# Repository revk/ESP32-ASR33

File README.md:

# ESP32-ASR33

Now at [Codeberg](https://codeberg.org/RevK/ESP32-ASR33)

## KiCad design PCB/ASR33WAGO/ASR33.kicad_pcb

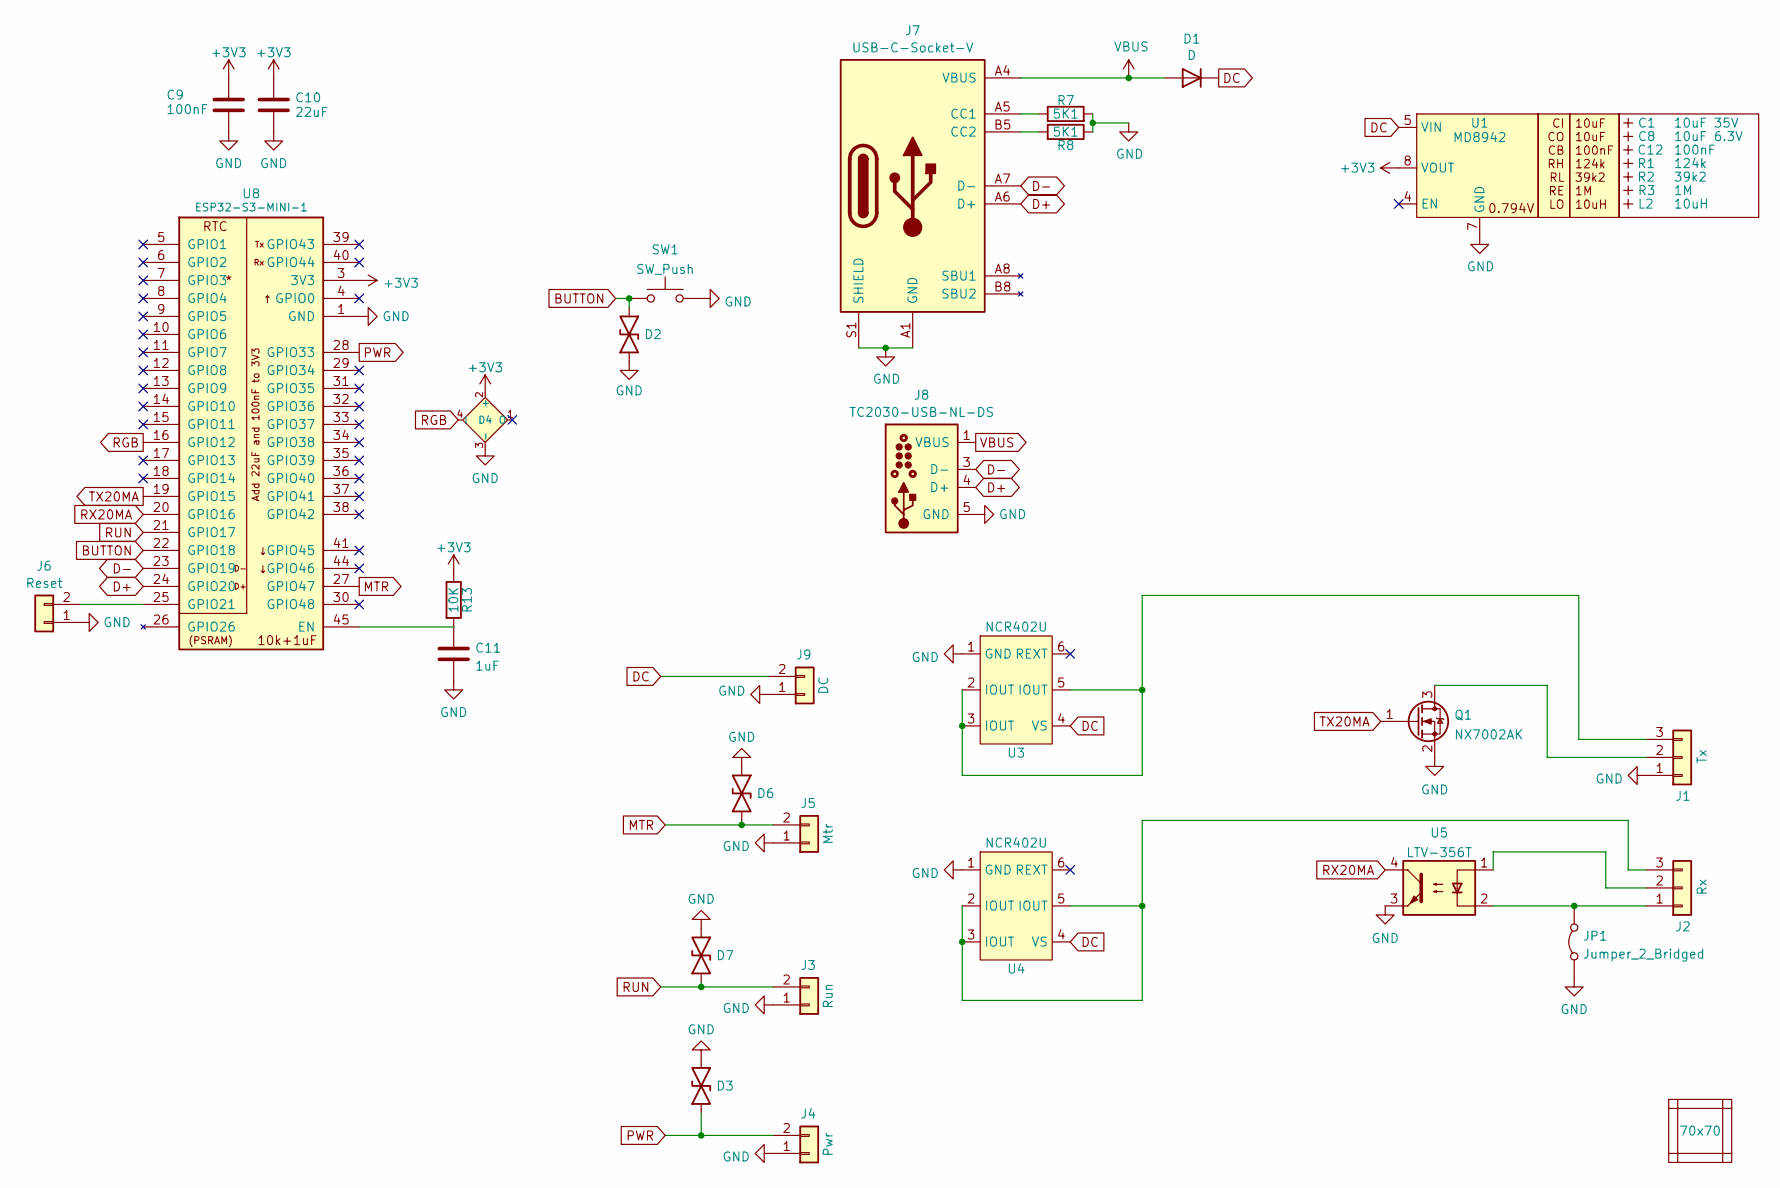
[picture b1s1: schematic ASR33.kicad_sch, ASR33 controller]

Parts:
C1: 10uF 35V; C_0603_; MPN C194427
C8: 10uF 6.3V; C_0603_; MPN C1691
C9: 100nF; C_0402
C10: 22uF; C_0402
C11: 1uF; C_0402
C12: 100nF; C_0603_
D1: D; D_SOD-123; MPN C1884542
D2, D3, D6, D7: DFN1006-2L; MPN C5137770
D4: XL-1010RGBC-WS2812B; SMD1010+; MPN C5349953
J1: Tx; WAGO-2060-453-998-404; MPN C2765056
J2: Rx; WAGO-2060-453-998-404; MPN C2765056
J3: Run; WAGO-2060-452-998-404; MPN C2765055
J4: Pwr; WAGO-2060-452-998-404; MPN C2765055
J5: Mtr; WAGO-2060-452-998-404; MPN C2765055
J6: Reset; AA-Pad
J7: USB-C-Socket-V; USB-C-Socket-H; MPN C709357
J8: TC2030-USB-NL-DS; Tag-Connect_TC2030-IDC-NL_2x03_P1.27mm_Vertical
J9: DC; WAGO-2060-452-998-404; MPN C2765055
JP1: Jumper_2_Bridged; Pad_1206_0805_Bridged
L2: 10uH; L_4x4_
PCB1: 70x70; PCB7070
Q1: NX7002AK; SOT-23
R1: 124k; R_0402_; MPN C138062
R2: 39k2; R_0402_
R3: 1M; R_0402_
R7, R8: 5K1; R_0402
R13: 10K; R_0402
SW1: SW_Push; TS-1092S-B3D2-G
U1: MD8942; SOT-23-6-MD8942; MPN C2684786
U3, U4: NCR402U; SOT-457; MPN C458148
U5: LTV-356T; SO-4_4.4x3.6mm_P2.54mm
U8: ESP32-S3-MINI-1; MPN C3013941
V1, V2, V3, V4: VCUT70N

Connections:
+3V3: C9.1, C10.1, D4.2 (+), R13.1, U1.8 (VOUT), U8.3 (3V3)
BUTTON: D2.1, SW1.2, U8.22 (GPIO18)
D+: J7.A6 (D+), J7.B6 (D+), J8.4 (D+), U8.24 (GPIO20)
D-: J7.A7 (D-), J7.B7 (D-), J8.3 (D-), U8.23 (GPIO19)
DC: D1.1 (K), J9.2, U1.5 (VIN), U3.4 (VS), U4.4 (VS)
GND: C9.2, C10.2, C11.2, D2.2, D3.2, D4.3 (-), D6.2, D7.2, J1.1, J3.1, J4.1, J5.1, J6.1, J7.A1 (GND), J7.A12 (GND), J7.B1 (GND), J7.B12 (GND), J7.S1 (SHIELD), J8.5 (GND), J8.6 (GND), J9.1, JP1.1 (A), Q1.2 (S), R7.2, R8.1, SW1.1, U1.2 (GND), U1.7 (GND), U3.1 (GND), U4.1 (GND), U5.3, U8.1 (GND), U8.2 (GND), U8.42 (GND), U8.43 (GND), U8.46 (GND), U8.47 (GND), U8.48 (GND), U8.49 (GND), U8.50 (GND), U8.51 (GND), U8.52 (GND), U8.53 (GND), U8.54 (GND), U8.55 (GND), U8.56 (GND), U8.57 (GND), U8.58 (GND), U8.59 (GND), U8.60 (GND), U8.61 (GND), U8.62 (GND), U8.63 (GND), U8.64 (GND), U8.65 (GND)
MTR: D6.1, J5.2, U8.27 (GPIO47)
unnamed: J1.2, Q1.3 (D)
unnamed: J1.3, U3.2 (IOUT), U3.3 (IOUT), U3.5 (IOUT)
unnamed: J2.1, JP1.2 (B), U5.2
unnamed: J2.2, U5.1
unnamed: J2.3, U4.2 (IOUT), U4.3 (IOUT), U4.5 (IOUT)
unnamed: J6.2, U8.25 (GPIO21)
unnamed: J7.A5 (CC1), R7.1
unnamed: J7.B5 (CC2), R8.2
unnamed: C11.1, R13.2, U8.45 (EN)
PWR: D3.1, J4.2, U8.28 (GPIO33)
RGB: D4.4 (I), U8.16 (GPIO12)
RUN: D7.1, J3.2, U8.21 (GPIO17)
RX20MA: U5.4, U8.20 (GPIO16)
TX20MA: Q1.1 (G), U8.19 (GPIO15)
VBUS: D1.2 (A), J7.A4 (VBUS), J7.A9 (VBUS), J7.B4 (VBUS), J7.B9 (VBUS), J8.1 (VBUS), J8.2 (VBUS)

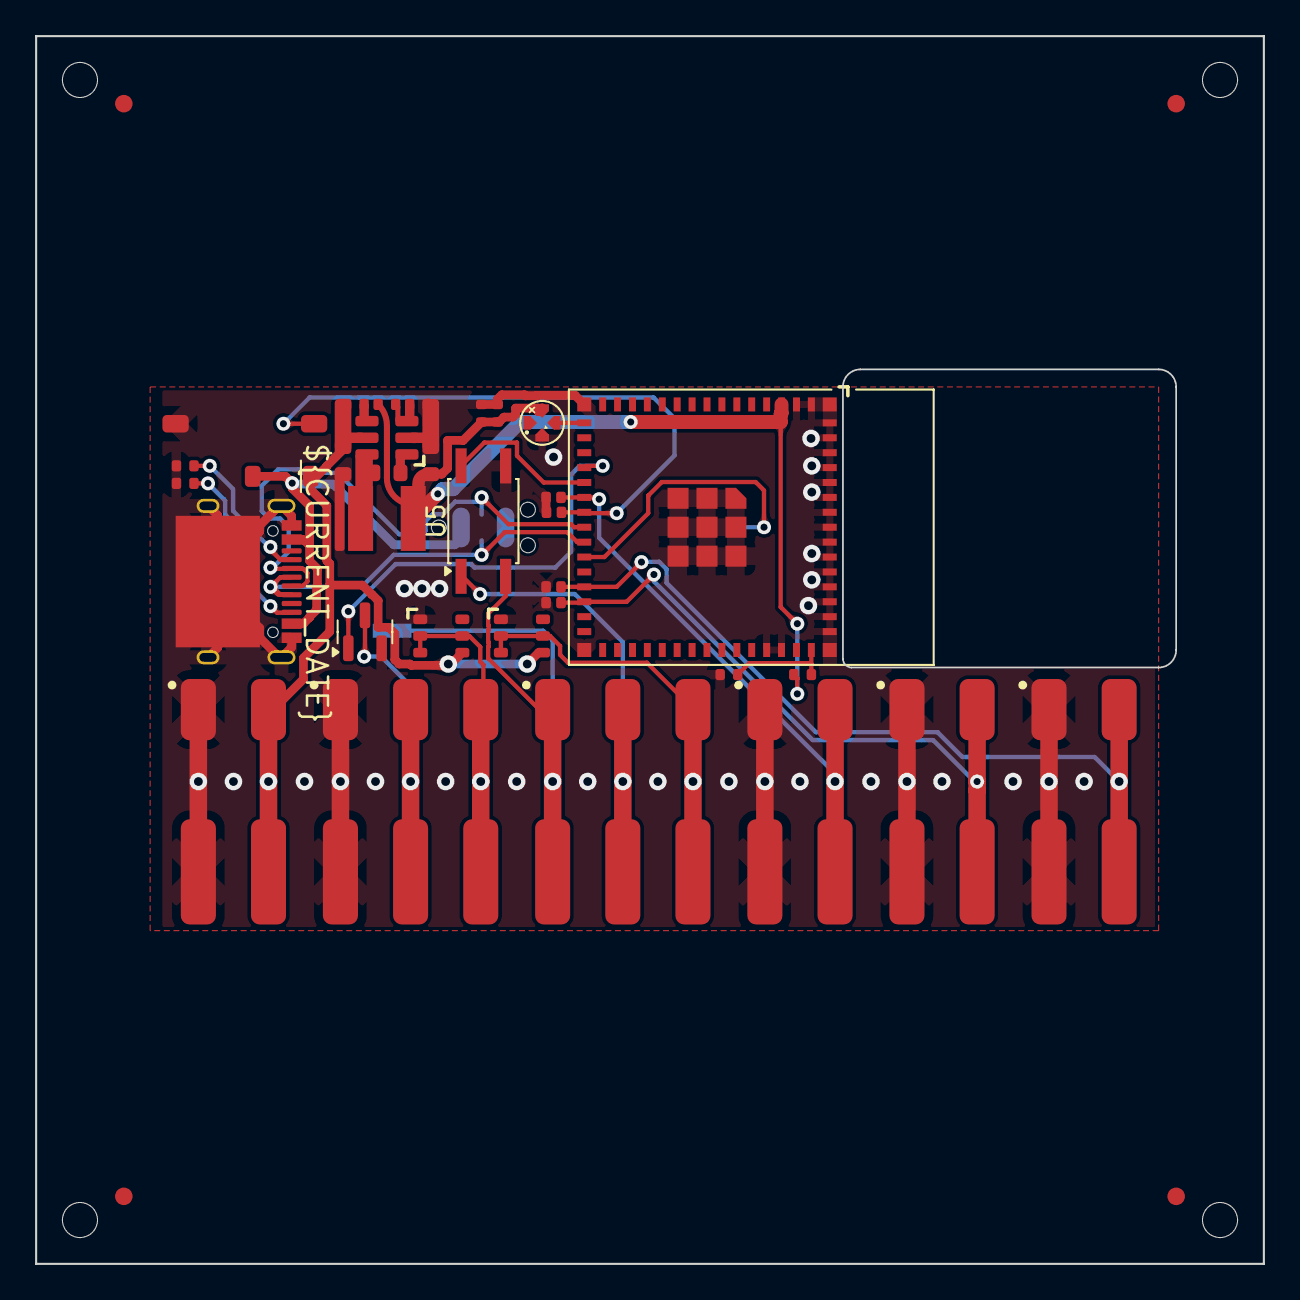
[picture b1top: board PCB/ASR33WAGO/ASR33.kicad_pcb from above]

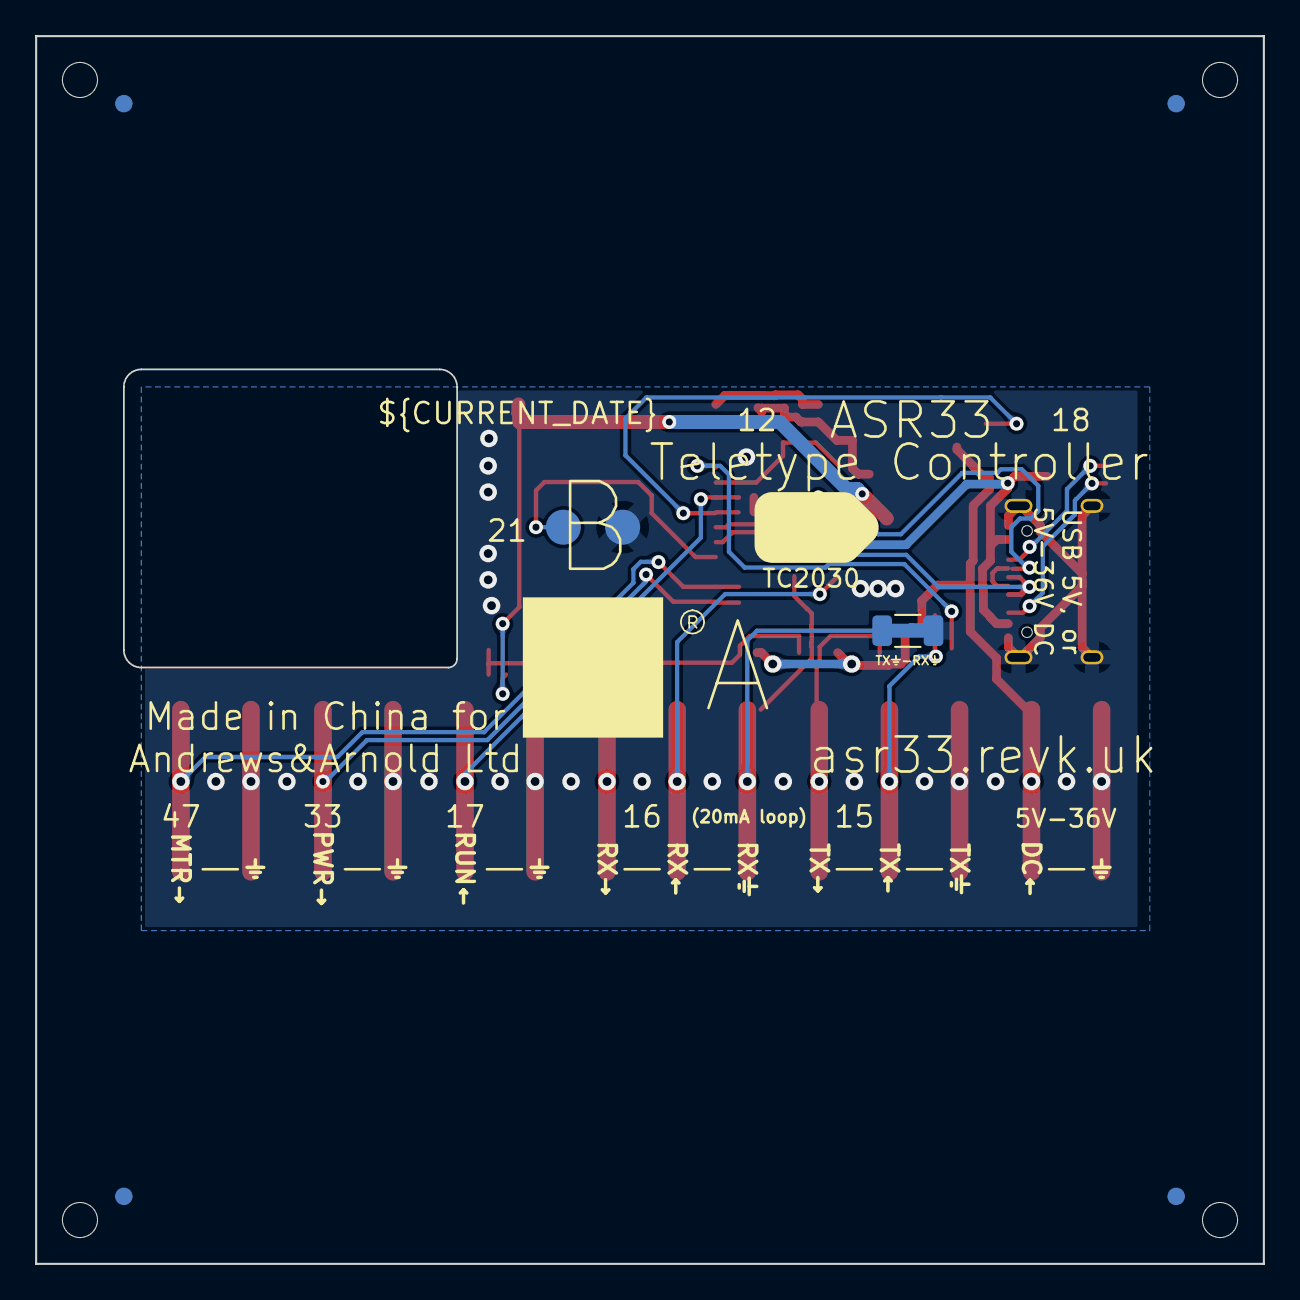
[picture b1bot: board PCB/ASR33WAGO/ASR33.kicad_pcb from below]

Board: 2 copper layers, 70.0 x 70.0 mm, 41 parts (3 on the bottom side), 22 nets.

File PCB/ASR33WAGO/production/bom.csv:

Designator,Footprint,Quantity,Value,LCSC Part #
C1,C_0603_,1,10uF 35V,C194427
C10,C_0402,1,22uF,
C11,C_0402,1,1uF,
C12,C_0603_,1,100nF,
C8,C_0603_,1,10uF 6.3V,C1691
C9,C_0402,1,100nF,
D1,D_SOD-123,1,D,C1884542
"D2, D3, D6, D7",DFN1006-2L,4,~,C5137770
D4,SMD1010+,1,XL-1010RGBC-WS2812B,C5349953
J1,WAGO-2060-453-998-404,1,Tx,C2765056
J2,WAGO-2060-453-998-404,1,Rx,C2765056
J3,WAGO-2060-452-998-404,1,Run,C2765055
J4,WAGO-2060-452-998-404,1,Pwr,C2765055
J5,WAGO-2060-452-998-404,1,Mtr,C2765055
J7,USB-C-Socket-H,1,USB-C-Socket-V,C709357
J9,WAGO-2060-452-998-404,1,DC,C2765055
L2,L_4x4_,1,10uH,
Q1,SOT-23,1,NX7002AK,
R1,R_0402_,1,124k,C138062
R13,R_0402,1,10K,
R2,R_0402_,1,39k2,
R3,R_0402_,1,1M,
"R7, R8",R_0402,2,5K1,
SW1,TS-1092S-B3D2-G,1,SW_Push,
U1,SOT-23-6-MD8942,1,MD8942,C2684786
"U3, U4",SOT-457,2,NCR402U,C458148
U5,SO-4_4.4x3.6mm_P2.54mm,1,LTV-356T,
U8,ESP32-S3-MINI-1,1,ESP32-S3-MINI-1,C3013941

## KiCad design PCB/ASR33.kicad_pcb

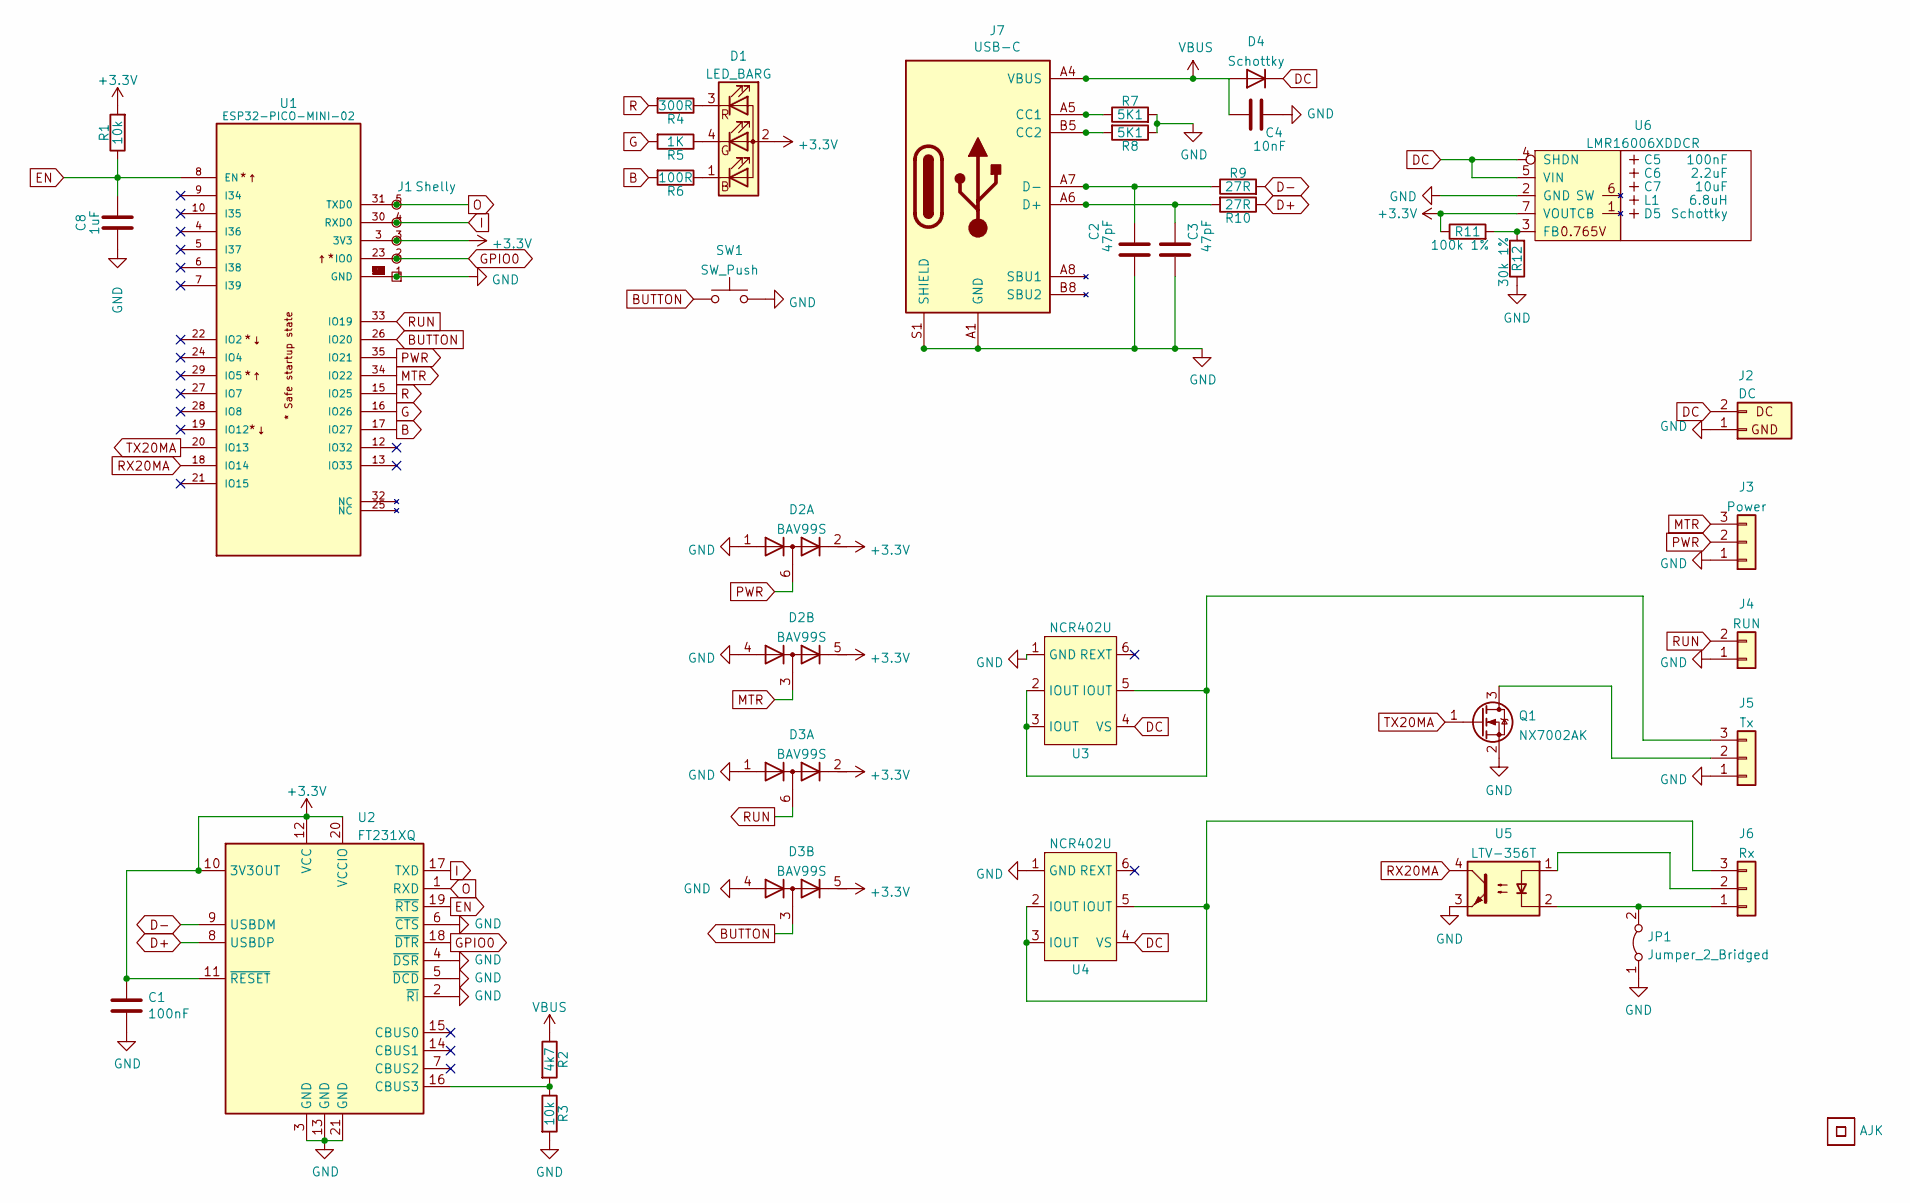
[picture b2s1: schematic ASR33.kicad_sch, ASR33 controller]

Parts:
C1: 100nF; C_0603
C2, C3: 47pF; C_0603
C4: 10nF; C_0603
C5: 100nF; C_0603_; LCSC Part # C30926
C6: 2.2uF; C_0805_; LCSC Part # C19110
C7: 10uF; C_0805_; LCSC Part # C17024
C8: 1uF; C_0603
D1: LED_BARG; MHS190RGBCT; LCSC Part # C409798
D2, D3: BAV99S; SOT-363_SC-70-6; JLCPCB Rotation Offset -90
D4: Schottky; D_1206; LCSC Part # C143805
D5: Schottky; D_1206_; LCSC Part # C143805
J1: Shelly
J2: DC; PTSM-HH1-2-RA
J3: Power; PTSM-HH1-3-RA
J4: RUN; PTSM-HH1-2-RA
J5: Tx; PTSM-HH1-3-RA
J6: Rx; PTSM-HH1-3-RA
J7: USB-C; USC16-TR; LCSC Part # C709357
JP1: Jumper_2_Bridged; Pad_1206_0805_Bridged
L1: 6.8uH; L_4x4_; LCSC Part # C354575
Logo1: AJK
Q1: NX7002AK; SOT-23; JLCPCB Rotation Offset 180
R1, R3: 10k; R_0603
R2: 4k7; R_0603
R4: 300R; R_0603; Part No 0603-680R
R5: 1K; R_0603; Part No 0603-2K
R6: 100R; R_0603; Part No 0603-220R
R7, R8: 5K1; R_0603
R9, R10: 27R; R_0603
R11: 100k 1%; R_0603; LCSC Part # C14675
R12: 30k 1%; R_0603; LCSC Part # C100001
SW1: SW_Push; SW_PUSH_6mm_PTH
U1: ESP32-PICO-MINI-02; PARTREV v1.0; LCSC Part # C2980306
U2: FT231XQ; QFN-20-1EP_4x4mm_P0.5mm_EP2.5x2.5mm; LCSC Part # C132159
U3, U4: NCR402U; SOT-457; JLCPCB Rotation Offset -90
U5: LTV-356T; SO-4_4.4x3.6mm_P2.54mm; JLCPCB Rotation Offset -90
U6: LMR16006XDDCR; SOT-23-Thin-6-Reg; Part No LMR16006XDDCR; LCSC Part # C87080
U7: QR; QR-ASR33

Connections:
+3V3: C1.1, D1.2 (A), D2.2 (K2), D2.5 (K4), D3.2 (K2), D3.5 (K4), J1.3 (3V3), R1.2, R11.1, U1.3 (3V3), U2.10 (3V3OUT), U2.11 (~RESET), U2.12 (VCC), U2.20 (VCCIO), U6.7 (VOUT)
B: R6.2, U1.17 (IO27)
BUTTON: D3.3 (K1A2), SW1.2, U1.26 (IO20)
D+: R10.1, U2.8 (USBDP)
D-: R9.2, U2.9 (USBDM)
DC: D4.1 (K), J2.2 (DC), U3.4 (VS), U4.4 (VS), U6.4 (SHDN), U6.5 (VIN)
EN: C8.2, R1.1, U1.8 (EN), U2.19 (~RTS)
G: R5.2, U1.16 (IO26)
GND: C1.2, C2.2, C3.2, C4.1, C8.1, D2.1 (A1), D2.4 (A3), D3.1 (A1), D3.4 (A3), J1.1 (GND), J2.1 (GND), J3.1, J4.1, J5.1, J7.A1 (GND), J7.A12 (GND), J7.B1 (GND), J7.B12 (GND), J7.S1 (SHIELD), JP1.1 (A), Q1.2 (S), R3.2, R7.2, R8.1, R12.1, SW1.1, U1.1 (GND), U1.2 (GND), U1.11 (GND), U1.14 (GND), U1.36 (GND), U1.37 (GND), U1.38 (GND), U1.39 (GND), U1.40 (GND), U1.41 (GND), U1.42 (GND), U1.43 (GND), U1.44 (GND), U1.45 (GND), U1.46 (GND), U1.47 (GND), U1.48 (GND), U1.49 (GND), U1.50 (GND), U1.51 (GND), U1.52 (GND), U1.53 (GND), U2.2 (~RI), U2.3 (GND), U2.4 (~DSR), U2.5 (~DCD), U2.6 (~CTS), U2.13 (GND), U2.21 (GND), U3.1 (GND), U4.1 (GND), U5.3, U6.2 (GND)
GPIO0: J1.2 (0), U1.23 (IO0), U2.18 (~DTR)
I: J1.4 (Rx), U1.30 (RXD0), U2.17 (TXD)
MTR: D2.3 (K1A2), J3.3, U1.34 (IO22)
unnamed: C2.1, J7.A7 (D-), J7.B7 (D-), R9.1
unnamed: C3.1, J7.A6 (D+), J7.B6 (D+), R10.2
unnamed: D1.1 (BK), R6.1
unnamed: D1.4 (GK), R5.1
unnamed: D1.3 (RK), R4.1
unnamed: J5.2, Q1.3 (D)
unnamed: J5.3, U3.2 (IOUT), U3.3 (IOUT), U3.5 (IOUT)
unnamed: J6.1, JP1.2 (B), U5.2
unnamed: J6.2, U5.1
unnamed: J6.3, U4.2 (IOUT), U4.3 (IOUT), U4.5 (IOUT)
unnamed: J7.A5 (CC1), R7.1
unnamed: J7.B5 (CC2), R8.2
unnamed: R2.2, R3.1, U2.16 (CBUS3)
unnamed: R11.2, R12.2, U6.3 (FB)
O: J1.5 (Tx), U1.31 (TXD0), U2.1 (RXD)
PWR: D2.6 (K3A4), J3.2, U1.35 (IO21)
R: R4.2, U1.15 (IO25)
RUN: D3.6 (K3A4), J4.2, U1.33 (IO19)
RX20MA: U1.18 (IO14), U5.4
TX20MA: Q1.1 (G), U1.20 (IO13)
VBUS: C4.2, D4.2 (A), J7.A4 (VBUS), J7.A9 (VBUS), J7.B4 (VBUS), J7.B9 (VBUS), R2.1

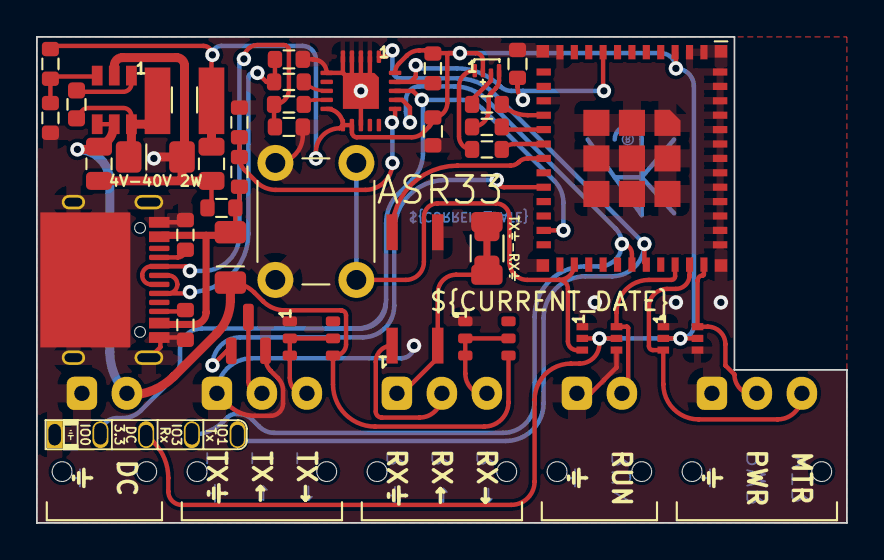
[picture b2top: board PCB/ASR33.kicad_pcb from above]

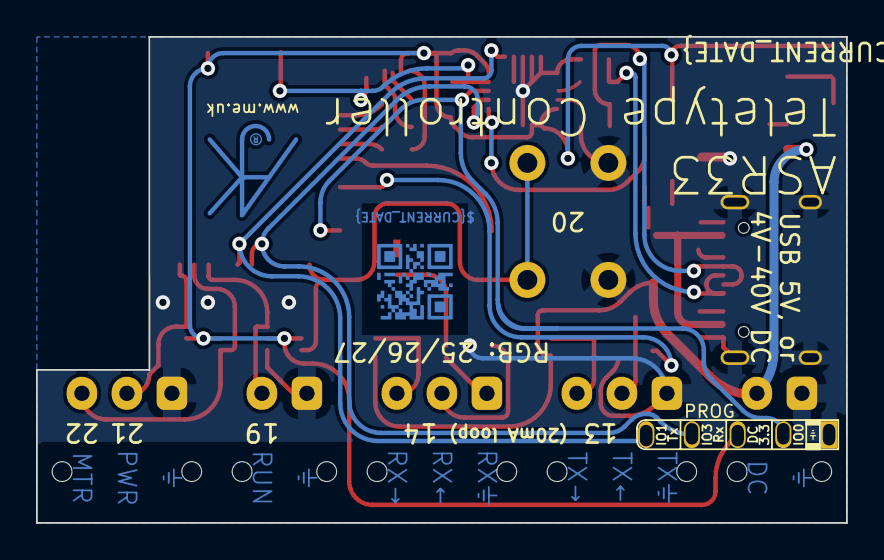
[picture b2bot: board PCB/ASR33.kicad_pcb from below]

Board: 2 copper layers, 45.0 x 27.0 mm, 44 parts (2 on the bottom side), 33 nets.

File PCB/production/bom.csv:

Designator,Footprint,Quantity,Value,LCSC Part #
C1,C_0603,1,100nF,
"C2, C3",C_0603,2,47pF,
C4,C_0603,1,10nF,
C5,C_0603_,1,100nF,C30926
C6,C_0805_,1,2.2uF,C19110
C7,C_0805_,1,10uF,C17024
D1,MHS190RGBCT,1,LED_BARG,C409798
"D2, D3",SOT-363_SC-70-6,2,BAV99S,
D4,D_1206,1,Schottky,C143805
D5,D_1206_,1,Schottky,C143805
J2,PTSM-HH1-2-RA,1,DC,
J3,PTSM-HH1-3-RA,1,Power,
J4,PTSM-HH1-2-RA,1,RUN,
J5,PTSM-HH1-3-RA,1,Tx,
J6,PTSM-HH1-3-RA,1,Rx,
J7,USC16-TR,1,USB-C,C709357
L1,L_4x4_,1,6.8uH,C354575
Q1,SOT-23,1,NX7002AK,
"R1, R3",R_0603,2,10k,
"R10, R9",R_0603,2,27R,
R11,R_0603,1,100k 1%,C14675
R12,R_0603,1,30k 1%,C100001
R2,R_0603,1,4k7,
R4,R_0603,1,300R,
R5,R_0603,1,1K,
R6,R_0603,1,100R,
"R7, R8",R_0603,2,5K1,
SW1,SW_PUSH_6mm_PTH,1,SW_Push,
U1,ESP32-PICO-MINI-02,1,ESP32-PICO-MINI-02,C2980306
U2,QFN-20-1EP_4x4mm_P0.5mm_EP2.5x2.5mm,1,FT231XQ,C132159
"U3, U4",SOT-457,2,NCR402U,
U5,SO-4_4.4x3.6mm_P2.54mm,1,LTV-356T,
U6,SOT-23-Thin-6-Reg,1,LMR16006XDDCR,C87080

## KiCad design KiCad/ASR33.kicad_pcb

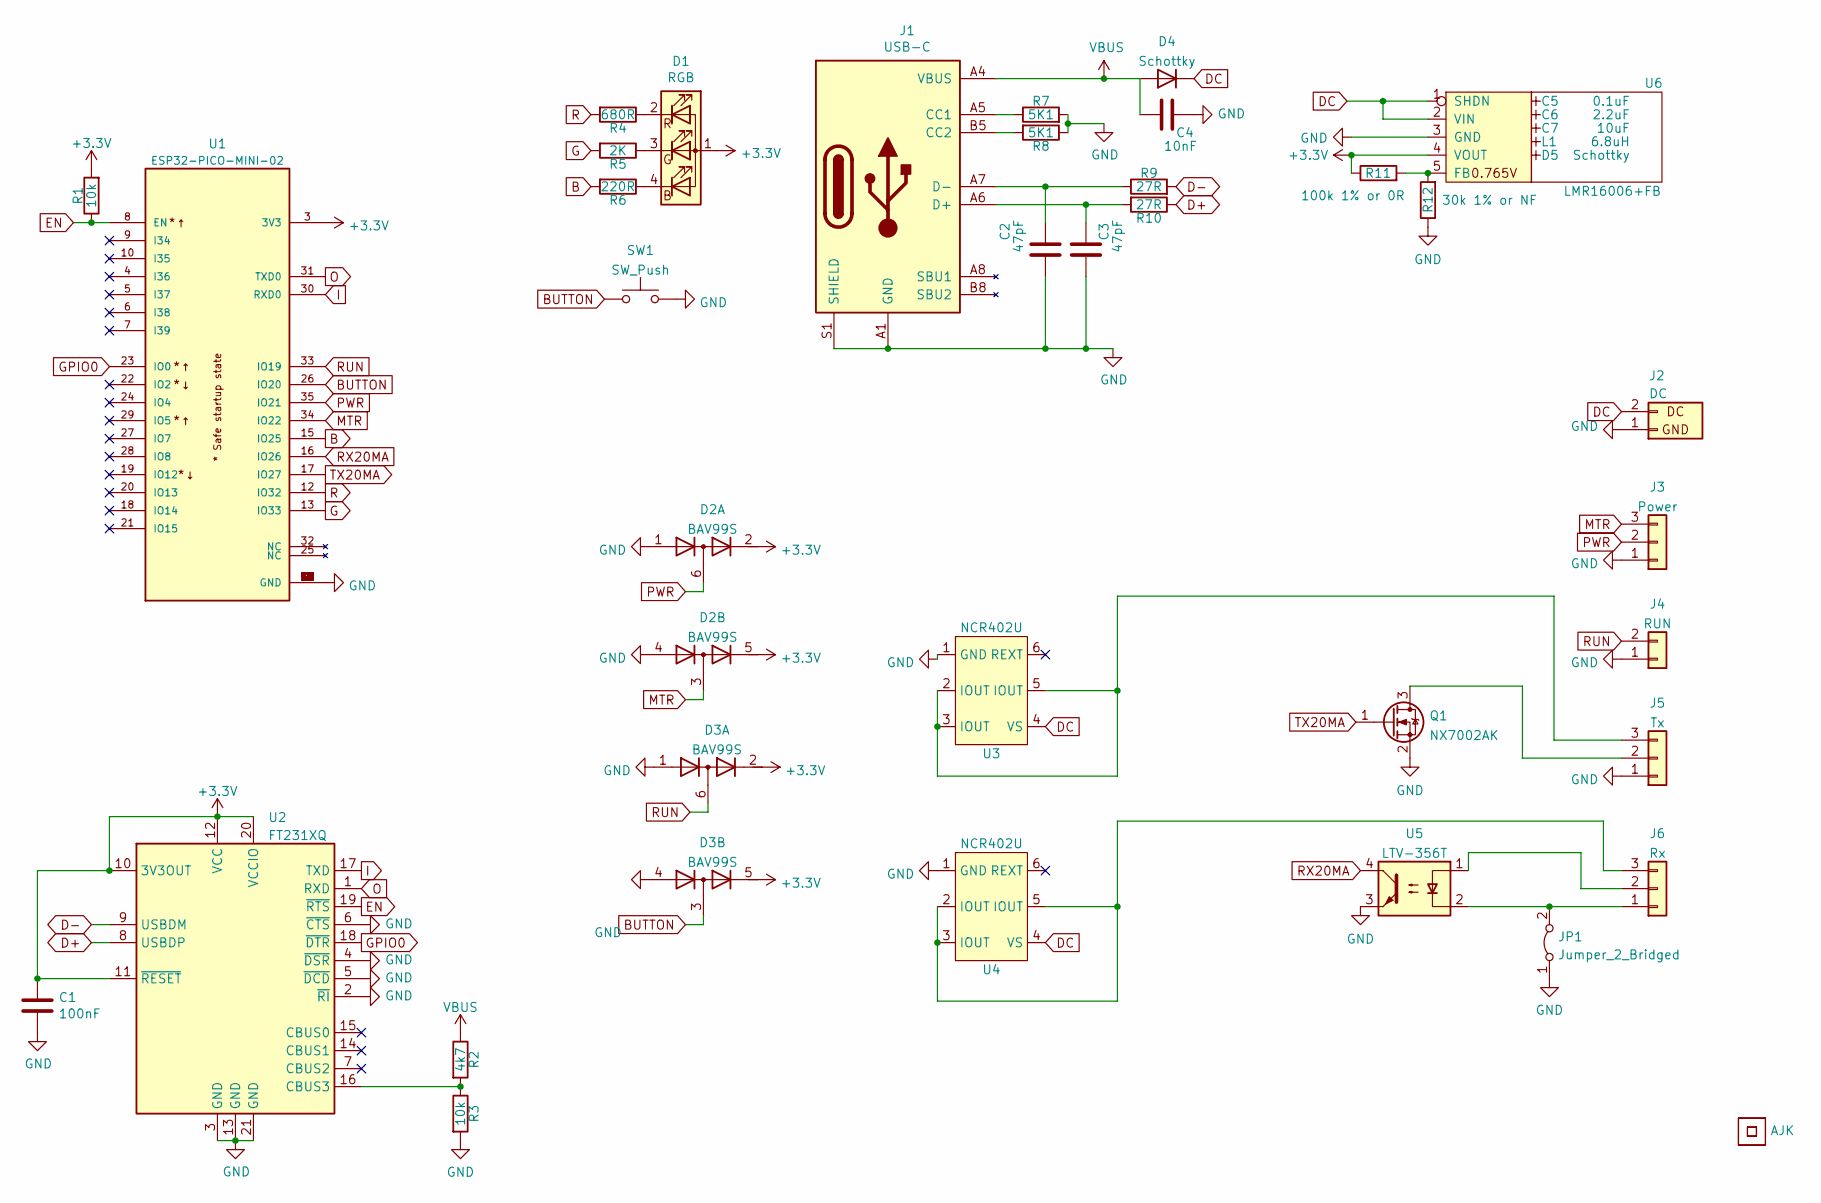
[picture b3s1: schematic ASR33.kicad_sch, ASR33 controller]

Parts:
C1: 100nF; C_0603
C2, C3: 47pF; C_0603
C4: 10nF; C_0603
C5: 0.1uF; Hidden
C6: 2.2uF; Hidden
C7: 10uF; Hidden
D1: RGB; LED-RGB-1.6x1.6; Part No APTF1616LSEEZGKQBKC
D2, D3: BAV99S; SOT-363_SC-70-6
D4: Schottky; D_1206
D5: Schottky; Hidden; Part No CD1206-B2100
J1: USB-C; USC16-TR-Round; Part No CSP-USC16-TR
J2: DC; Molex_MiniSPOX_H2RA
J3: Power; Molex_MiniSPOX_H3RA
J4: RUN; Molex_MiniSPOX_H2RA
J5: Tx; Molex_MiniSPOX_H3RA
J6: Rx; Molex_MiniSPOX_H3RA
JP1: Jumper_2_Bridged; Pad_1206_0805_Bridged
L1: 6.8uH; Hidden; Part No TYA4020
Logo1: AJK
Q1: NX7002AK; SOT-23
R1, R3: 10k; R_0603
R2: 4k7; R_0603
R4: 680R; R_0603
R5: 2K; R_0603
R6: 220R; R_0603
R7, R8: 5K1; R_0603
R9, R10: 27R; R_0603
R11: 100k 1% or 0R; R_0603
R12: 30k 1% or NF; R_0603
SW1: SW_Push; SW_PUSH_6mm_PTH
U1: ESP32-PICO-MINI-02; PARTREV v1.0
U2: FT231XQ; QFN-20-1EP_4x4mm_P0.5mm_EP2.5x2.5mm
U3, U4: NCR402U; SOT-457
U5: LTV-356T; SO-4_4.4x3.6mm_P2.54mm
U6: LMR16006+FB; RegulatorBlockFB; Part No LMR16006YQ3
U7: QR; QR-ASR33

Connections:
+3V3: C1.1, D1.1 (A), D2.2 (K2), D2.5 (K4), D3.2 (K2), D3.5 (K4), R1.2, R11.1, U1.3 (3V3), U2.10 (3V3OUT), U2.11 (~RESET), U2.12 (VCC), U2.20 (VCCIO), U6.4 (VOUT)
B: R6.2, U1.15 (IO25)
BUTTON: D3.3 (K1A2), SW1.2, U1.26 (IO20)
D+: R10.1, U2.8 (USBDP)
D-: R9.2, U2.9 (USBDM)
DC: D4.1 (K), J2.2 (DC), U3.4 (VS), U4.4 (VS), U6.1 (SHDN), U6.2 (VIN)
EN: R1.1, U1.8 (EN), U2.19 (~RTS)
G: R5.2, U1.13 (IO33)
GND: C1.2, C2.2, C3.2, C4.1, D2.1 (A1), D2.4 (A3), D3.1 (A1), D3.4 (A3), J1.A1 (GND), J1.A12 (GND), J1.B1 (GND), J1.B12 (GND), J1.S1 (SHIELD), J2.1 (GND), J3.1, J4.1, J5.1, JP1.1 (A), Q1.2 (S), R3.2, R7.2, R8.1, R12.1, SW1.1, U1.1 (GND), U1.2 (GND), U1.11 (GND), U1.14 (GND), U1.36 (GND), U1.37 (GND), U1.38 (GND), U1.39 (GND), U1.40 (GND), U1.41 (GND), U1.42 (GND), U1.43 (GND), U1.44 (GND), U1.45 (GND), U1.46 (GND), U1.47 (GND), U1.48 (GND), U1.49 (GND), U1.50 (GND), U1.51 (GND), U1.52 (GND), U1.53 (GND), U2.2 (~RI), U2.3 (GND), U2.4 (~DSR), U2.5 (~DCD), U2.6 (~CTS), U2.13 (GND), U2.21 (GND), U3.1 (GND), U4.1 (GND), U5.3, U6.3 (GND)
GPIO0: U1.23 (IO0), U2.18 (~DTR)
I: U1.30 (RXD0), U2.17 (TXD)
MTR: D2.3 (K1A2), J3.3, U1.34 (IO22)
unnamed: C2.1, J1.A7 (D-), J1.B7 (D-), R9.1
unnamed: C3.1, J1.A6 (D+), J1.B6 (D+), R10.2
unnamed: D1.2 (RK), R4.1
unnamed: D1.3 (GK), R5.1
unnamed: D1.4 (BK), R6.1
unnamed: J1.A5 (CC1), R7.1
unnamed: J1.B5 (CC2), R8.2
unnamed: J5.2, Q1.3 (D)
unnamed: J5.3, U3.2 (IOUT), U3.3 (IOUT), U3.5 (IOUT)
unnamed: J6.1, JP1.2 (B), U5.2
unnamed: J6.2, U5.1
unnamed: J6.3, U4.2 (IOUT), U4.3 (IOUT), U4.5 (IOUT)
unnamed: R2.2, R3.1, U2.16 (CBUS3)
unnamed: R11.2, R12.2, U6.5 (FB)
O: U1.31 (TXD0), U2.1 (RXD)
PWR: D2.6 (K3A4), J3.2, U1.35 (IO21)
R: R4.2, U1.12 (IO32)
RUN: D3.6 (K3A4), J4.2, U1.33 (IO19)
RX20MA: U1.16 (IO26), U5.4
TX20MA: Q1.1 (G), U1.17 (IO27)
VBUS: C4.2, D4.2 (A), J1.A4 (VBUS), J1.A9 (VBUS), J1.B4 (VBUS), J1.B9 (VBUS), R2.1

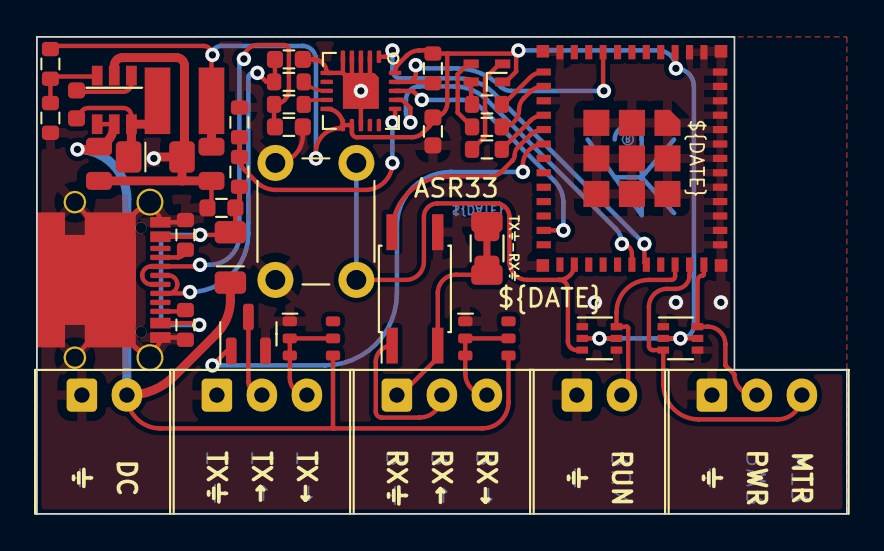
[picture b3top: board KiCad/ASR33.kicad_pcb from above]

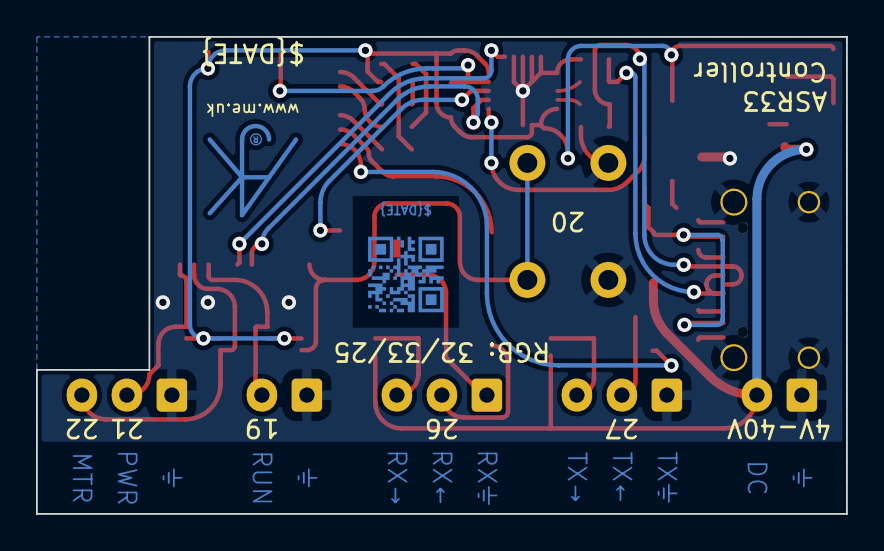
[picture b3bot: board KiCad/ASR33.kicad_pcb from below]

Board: 2 copper layers, 45.0 x 26.5 mm, 42 parts (2 on the bottom side), 33 nets.

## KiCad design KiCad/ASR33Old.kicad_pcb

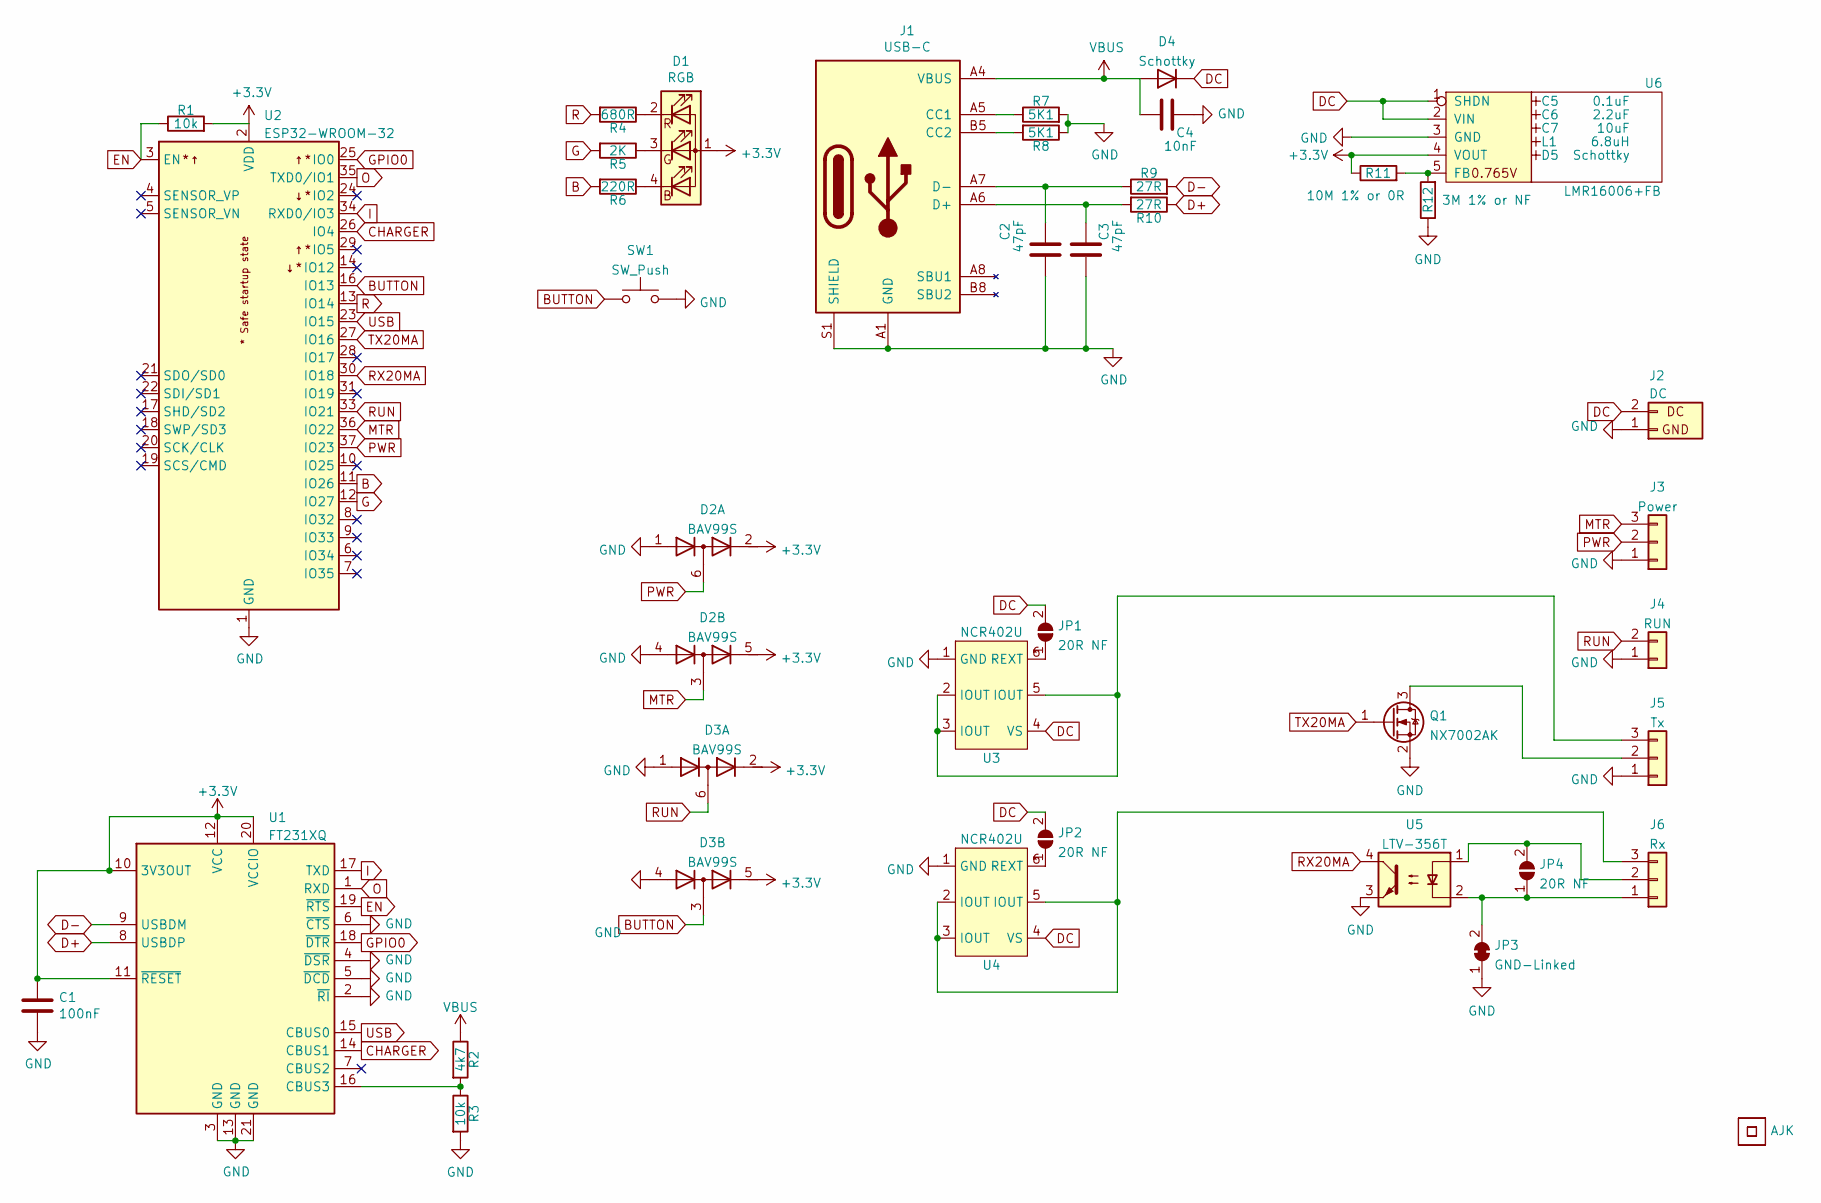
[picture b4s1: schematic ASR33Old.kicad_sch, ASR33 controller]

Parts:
C1: 100nF; C_0603
C2, C3: 47pF; C_0603
C4: 10nF; C_0603
C5: 0.1uF; Hidden
C6: 2.2uF; Hidden
C7: 10uF; Hidden
D1: RGB; LED-RGB-1.6x1.6; Part No APTF1616LSEEZGKQBKC
D2, D3: BAV99S; SOT-363_SC-70-6
D4: Schottky; D_1206_3216Metric
D5: Schottky; Hidden; Part No CD1206-B2100
J1: USB-C; USC16-TR-Round; Part No CSP-USC16-TR
J2: DC; Molex_MiniSPOX_H2RA
J3: Power; Molex_MiniSPOX_H3RA
J4: RUN; Molex_MiniSPOX_H2RA
J5: Tx; Molex_MiniSPOX_H3RA
J6: Rx; Molex_MiniSPOX_H3RA
JP1, JP2, JP4: 20R NF; Pad_1206_0805_Open
JP3: GND-Linked; Pad_1206_0805_Bridged
L1: 6.8uH; Hidden; Part No TYA4020
Logo1: AJK
Q1: NX7002AK; SOT-23
R1, R3: 10k; R_0603
R2: 4k7; R_0603
R4: 680R; R_0603
R5: 2K; R_0603
R6: 220R; R_0603
R7, R8: 5K1; R_0603
R9, R10: 27R; R_0603
R11: 10M 1% or 0R; R_0603
R12: 3M 1% or NF; R_0603
SW1: SW_Push; SW_PUSH_6mm_PTH
U1: FT231XQ; QFN-20-1EP_4x4mm_P0.5mm_EP2.5x2.5mm
U2: ESP32-WROOM-32
U3, U4: NCR402U; SOT-457
U5: LTV-356T; SO-4_4.4x3.6mm_P2.54mm
U6: LMR16006+FB; RegulatorBlockFB; Part No LMR16006YQ3
U7: QR; QR-ASR33

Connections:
+3V3: C1.1, D1.1 (A), D2.2 (K2), D2.5 (K4), D3.2 (K2), D3.5 (K4), R1.2, R11.1, U1.10 (3V3OUT), U1.11 (~RESET), U1.12 (VCC), U1.20 (VCCIO), U2.2 (VDD), U6.4 (VOUT)
B: R6.2, U2.11 (IO26)
BUTTON: D3.3 (K1A2), SW1.2, U2.16 (IO13)
CHARGER: U1.14 (CBUS1), U2.26 (IO4)
D+: R10.1, U1.8 (USBDP)
D-: R9.2, U1.9 (USBDM)
DC: D4.1 (K), J2.2 (DC), JP1.2 (B), JP2.2 (B), U3.4 (VS), U4.4 (VS), U6.1 (SHDN), U6.2 (VIN)
EN: R1.1, U1.19 (~RTS), U2.3 (EN)
G: R5.2, U2.12 (IO27)
GND: C1.2, C2.2, C3.2, C4.1, D2.1 (A1), D2.4 (A3), D3.1 (A1), D3.4 (A3), J1.A1 (GND), J1.A12 (GND), J1.B1 (GND), J1.B12 (GND), J1.S1 (SHIELD), J2.1 (GND), J3.1, J4.1, J5.1, JP3.1 (A), Q1.2 (S), R3.2, R7.2, R8.1, R12.1, SW1.1, U1.2 (~RI), U1.3 (GND), U1.4 (~DSR), U1.5 (~DCD), U1.6 (~CTS), U1.13 (GND), U1.21 (GND), U2.1 (GND), U2.15 (GND), U2.38 (GND), U2.39 (GND), U3.1 (GND), U4.1 (GND), U5.3, U6.3 (GND)
GPIO0: U1.18 (~DTR), U2.25 (IO0)
I: U1.17 (TXD), U2.34 (RXD0/IO3)
MTR: D2.3 (K1A2), J3.3, U2.36 (IO22)
unnamed: C2.1, J1.A7 (D-), J1.B7 (D-), R9.1
unnamed: C3.1, J1.A6 (D+), J1.B6 (D+), R10.2
unnamed: D1.2 (RK), R4.1
unnamed: D1.3 (GK), R5.1
unnamed: D1.4 (BK), R6.1
unnamed: J1.A5 (CC1), R7.1
unnamed: J1.B5 (CC2), R8.2
unnamed: J5.2, Q1.3 (D)
unnamed: J5.3, U3.2 (IOUT), U3.3 (IOUT), U3.5 (IOUT)
unnamed: J6.1, JP3.2 (B), JP4.1 (A), U5.2
unnamed: J6.2, JP4.2 (B), U5.1
unnamed: J6.3, U4.2 (IOUT), U4.3 (IOUT), U4.5 (IOUT)
unnamed: JP1.1 (A), U3.6 (REXT)
unnamed: JP2.1 (A), U4.6 (REXT)
unnamed: R2.2, R3.1, U1.16 (CBUS3)
unnamed: R11.2, R12.2, U6.5 (FB)
O: U1.1 (RXD), U2.35 (TXD0/IO1)
PWR: D2.6 (K3A4), J3.2, U2.37 (IO23)
R: R4.2, U2.13 (IO14)
RUN: D3.6 (K3A4), J4.2, U2.33 (IO21)
RX20MA: U2.30 (IO18), U5.4
TX20MA: Q1.1 (G), U2.27 (IO16)
USB: U1.15 (CBUS0), U2.23 (IO15)
VBUS: C4.2, D4.2 (A), J1.A4 (VBUS), J1.A9 (VBUS), J1.B4 (VBUS), J1.B9 (VBUS), R2.1
